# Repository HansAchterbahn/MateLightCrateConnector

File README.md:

# MateLight-CrateConnector

This repo is an addition to the MateLightScrewCap and enhances it with a crate connector PCB. The PCB not only allows easy connection of the crates, but also easy power supply between the crates. This is useful to avoid power transfer problems, voltage drops and heat problems.

In this repository you will find the schematics and board layouts created in KiCad. You will also find a 3D model of the circuit board.

*Fork me and have fun!*

**MateLight of CCC youth group Göttingen at the 36c3 event 2019 in Leipzig**

## 3D View

- FreeCAD Model: [3d/MateLightCrateConnector.FCStd](https://github.com/HansAchterbahn/MateLightCrateConnector/blob/master/3d/MateLightCrateConnector.FCStd)
- Animated 3D STL model: [3d/MateLightCrateConnector.stl](https://github.com/HansAchterbahn/MateLightCrateConnector/blob/master/3d/MateLightCrateConnector.stl)

__Top view__

__Bottom view__

## Schematic

## Board

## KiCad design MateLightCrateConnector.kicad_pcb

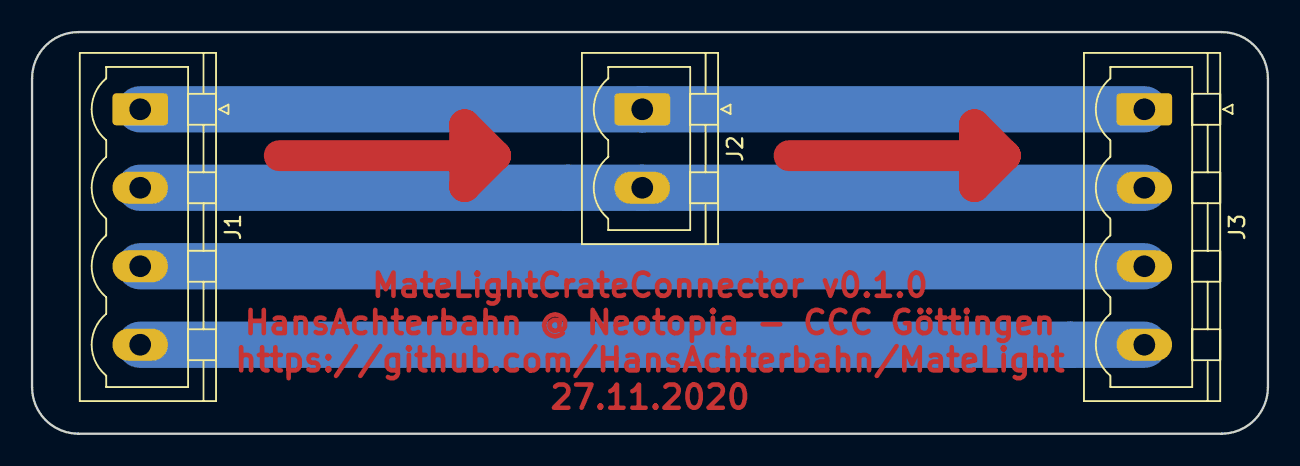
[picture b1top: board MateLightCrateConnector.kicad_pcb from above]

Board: 2 copper layers, 80.0 x 26.0 mm, 3 parts (0 on the bottom side), 4 nets.

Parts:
J1, J3: Conn_01x04; PhoenixContact_MSTBVA_2,5_4-G-5,08_1x04_P5.08mm_Vertical
J2: Conn_01x02; PhoenixContact_MSTBVA_2,5_2-G-5,08_1x02_P5.08mm_Vertical

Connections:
/5V: J1.1, J2.1, J3.1
/CLK: J1.3, J3.3
/DATA: J1.4, J3.4
/GND: J1.2, J2.2, J3.2

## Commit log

2020-11-30 Init Repo with License
2020-11-30 Created version v0.1.0 with Gerber data and documentation
2020-11-30 Doc: changed broken link | renamed folder doku to doc
2020-11-30 doc: small changes in 3D View
2020-11-30 Doc: Added pic of MateLight on 36c3
2021-02-27 Added ZIP for manufacturing
